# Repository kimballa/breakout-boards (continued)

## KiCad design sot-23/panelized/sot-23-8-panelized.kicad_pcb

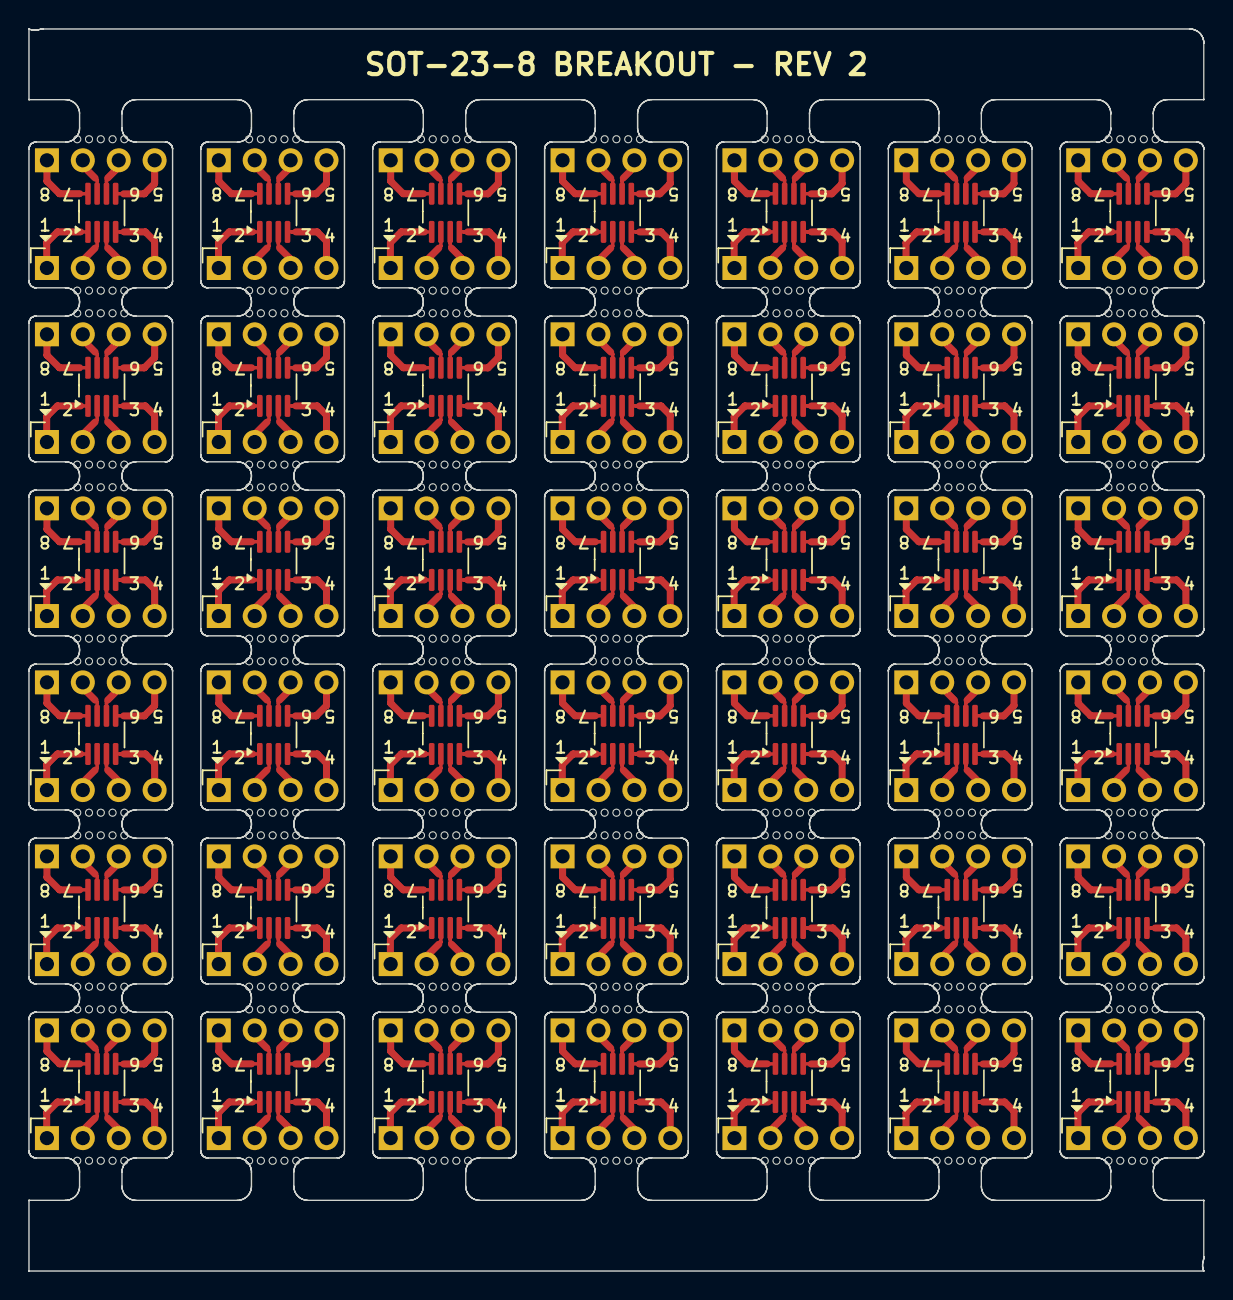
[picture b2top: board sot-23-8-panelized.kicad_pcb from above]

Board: 2 copper layers, 83.1 x 87.9 mm, 546 parts (0 on the bottom side), 336 nets.

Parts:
J3, J3#2, J3#3, J3#4, J3#5, J3#6, J3#7, J3#8, J3#9, J3#10, J3#11, J3#12, J3#13, J3#14, J3#15, J3#16, J3#17, J3#18, J3#19, J3#20, J3#21, J3#22, J3#23, J3#24, J3#25, J3#26, J3#27, J3#28, J3#29, J3#30, J3#31, J3#32, J3#33, J3#34, J3#35, J3#36, J3#37, J3#38, J3#39, J3#40, J3#41, J3#42, J4, J4#2, J4#3, J4#4, J4#5, J4#6, J4#7, J4#8, J4#9, J4#10, J4#11, J4#12, J4#13, J4#14, J4#15, J4#16, J4#17, J4#18, J4#19, J4#20, J4#21, J4#22, J4#23, J4#24, J4#25, J4#26, J4#27, J4#28, J4#29, J4#30, J4#31, J4#32, J4#33, J4#34, J4#35, J4#36, J4#37, J4#38, J4#39, J4#40, J4#41, J4#42: Conn_01x04; PinHeader_1x04_P2.54mm_Vertical
KiKit_MB_1_2, KiKit_MB_1_3, KiKit_MB_1_4, KiKit_MB_1_5, KiKit_MB_1_6, KiKit_MB_2_2, KiKit_MB_2_3, KiKit_MB_2_4, KiKit_MB_2_5, KiKit_MB_2_6, KiKit_MB_3_2, KiKit_MB_3_3, KiKit_MB_3_4, KiKit_MB_3_5, KiKit_MB_3_6, KiKit_MB_4_2, KiKit_MB_4_3, KiKit_MB_4_4, KiKit_MB_4_5, KiKit_MB_4_6, KiKit_MB_5_2, KiKit_MB_5_3, KiKit_MB_5_4, KiKit_MB_5_5, KiKit_MB_5_6, KiKit_MB_6_2, KiKit_MB_6_3, KiKit_MB_6_4, KiKit_MB_6_5, KiKit_MB_6_6, KiKit_MB_7_2, KiKit_MB_7_3, KiKit_MB_7_4, KiKit_MB_7_5, KiKit_MB_7_6, KiKit_MB_8_2, KiKit_MB_8_3, KiKit_MB_8_4, KiKit_MB_8_5, KiKit_MB_8_6, KiKit_MB_9_2, KiKit_MB_9_3, KiKit_MB_9_4, KiKit_MB_9_5, KiKit_MB_9_6, KiKit_MB_10_2, KiKit_MB_10_3, KiKit_MB_10_4, KiKit_MB_10_5, KiKit_MB_10_6, KiKit_MB_11_2, KiKit_MB_11_3, KiKit_MB_11_4, KiKit_MB_11_5, KiKit_MB_11_6, KiKit_MB_12_2, KiKit_MB_12_3, KiKit_MB_12_4, KiKit_MB_12_5, KiKit_MB_12_6, KiKit_MB_13_2, KiKit_MB_13_3, KiKit_MB_13_4, KiKit_MB_13_5, KiKit_MB_13_6, KiKit_MB_14_2, KiKit_MB_14_3, KiKit_MB_14_4, KiKit_MB_14_5, KiKit_MB_14_6, KiKit_MB_15_2, KiKit_MB_15_3, KiKit_MB_15_4, KiKit_MB_15_5, KiKit_MB_15_6, KiKit_MB_16_2, KiKit_MB_16_3, KiKit_MB_16_4, KiKit_MB_16_5, KiKit_MB_16_6, KiKit_MB_17_2, KiKit_MB_17_3, KiKit_MB_17_4, KiKit_MB_17_5, KiKit_MB_17_6, KiKit_MB_18_2, KiKit_MB_18_3, KiKit_MB_18_4, KiKit_MB_18_5, KiKit_MB_18_6, KiKit_MB_19_2, KiKit_MB_19_3, KiKit_MB_19_4, KiKit_MB_19_5, KiKit_MB_19_6, KiKit_MB_20_2, KiKit_MB_20_3, KiKit_MB_20_4, KiKit_MB_20_5, KiKit_MB_20_6, KiKit_MB_21_2, KiKit_MB_21_3, KiKit_MB_21_4, KiKit_MB_21_5, KiKit_MB_21_6, KiKit_MB_22_2, KiKit_MB_22_3, KiKit_MB_22_4, KiKit_MB_22_5, KiKit_MB_22_6, KiKit_MB_23_2, KiKit_MB_23_3, KiKit_MB_23_4, KiKit_MB_23_5, KiKit_MB_23_6, KiKit_MB_24_2, KiKit_MB_24_3, KiKit_MB_24_4, KiKit_MB_24_5, KiKit_MB_24_6, KiKit_MB_25_2, KiKit_MB_25_3, KiKit_MB_25_4, KiKit_MB_25_5, KiKit_MB_25_6, KiKit_MB_26_2, KiKit_MB_26_3, KiKit_MB_26_4, KiKit_MB_26_5, KiKit_MB_26_6, KiKit_MB_27_2, KiKit_MB_27_3, KiKit_MB_27_4, KiKit_MB_27_5, KiKit_MB_27_6, KiKit_MB_28_2, KiKit_MB_28_3, KiKit_MB_28_4, KiKit_MB_28_5, KiKit_MB_28_6, KiKit_MB_29_2, KiKit_MB_29_3, KiKit_MB_29_4, KiKit_MB_29_5, KiKit_MB_29_6, KiKit_MB_30_2, KiKit_MB_30_3, KiKit_MB_30_4, KiKit_MB_30_5, KiKit_MB_30_6, KiKit_MB_31_2, KiKit_MB_31_3, KiKit_MB_31_4, KiKit_MB_31_5, KiKit_MB_31_6, KiKit_MB_32_2, KiKit_MB_32_3, KiKit_MB_32_4, KiKit_MB_32_5, KiKit_MB_32_6, KiKit_MB_33_2, KiKit_MB_33_3, KiKit_MB_33_4, KiKit_MB_33_5, KiKit_MB_33_6, KiKit_MB_34_2, KiKit_MB_34_3, KiKit_MB_34_4, KiKit_MB_34_5, KiKit_MB_34_6, KiKit_MB_35_2, KiKit_MB_35_3, KiKit_MB_35_4, KiKit_MB_35_5, KiKit_MB_35_6, KiKit_MB_36_2, KiKit_MB_36_3, KiKit_MB_36_4, KiKit_MB_36_5, KiKit_MB_36_6, KiKit_MB_37_2, KiKit_MB_37_3, KiKit_MB_37_4, KiKit_MB_37_5, KiKit_MB_37_6, KiKit_MB_38_2, KiKit_MB_38_3, KiKit_MB_38_4, KiKit_MB_38_5, KiKit_MB_38_6, KiKit_MB_39_2, KiKit_MB_39_3, KiKit_MB_39_4, KiKit_MB_39_5, KiKit_MB_39_6, KiKit_MB_40_2, KiKit_MB_40_3, KiKit_MB_40_4, KiKit_MB_40_5, KiKit_MB_40_6, KiKit_MB_41_2, KiKit_MB_41_3, KiKit_MB_41_4, KiKit_MB_41_5, KiKit_MB_41_6, KiKit_MB_42_2, KiKit_MB_42_3, KiKit_MB_42_4, KiKit_MB_42_5, KiKit_MB_42_6, KiKit_MB_43_2, KiKit_MB_43_3, KiKit_MB_43_4, KiKit_MB_43_5, KiKit_MB_43_6, KiKit_MB_44_2, KiKit_MB_44_3, KiKit_MB_44_4, KiKit_MB_44_5, KiKit_MB_44_6, KiKit_MB_45_2, KiKit_MB_45_3, KiKit_MB_45_4, KiKit_MB_45_5, KiKit_MB_45_6, KiKit_MB_46_2, KiKit_MB_46_3, KiKit_MB_46_4, KiKit_MB_46_5, KiKit_MB_46_6, KiKit_MB_47_2, KiKit_MB_47_3, KiKit_MB_47_4, KiKit_MB_47_5, KiKit_MB_47_6, KiKit_MB_48_2, KiKit_MB_48_3, KiKit_MB_48_4, KiKit_MB_48_5, KiKit_MB_48_6, KiKit_MB_49_2, KiKit_MB_49_3, KiKit_MB_49_4, KiKit_MB_49_5, KiKit_MB_49_6, KiKit_MB_50_2, KiKit_MB_50_3, KiKit_MB_50_4, KiKit_MB_50_5, KiKit_MB_50_6, KiKit_MB_51_2, KiKit_MB_51_3, KiKit_MB_51_4, KiKit_MB_51_5, KiKit_MB_51_6, KiKit_MB_52_2, KiKit_MB_52_3, KiKit_MB_52_4, KiKit_MB_52_5, KiKit_MB_52_6, KiKit_MB_53_2, KiKit_MB_53_3, KiKit_MB_53_4, KiKit_MB_53_5, KiKit_MB_53_6, KiKit_MB_54_2, KiKit_MB_54_3, KiKit_MB_54_4, KiKit_MB_54_5, KiKit_MB_54_6, KiKit_MB_55_2, KiKit_MB_55_3, KiKit_MB_55_4, KiKit_MB_55_5, KiKit_MB_55_6, KiKit_MB_56_2, KiKit_MB_56_3, KiKit_MB_56_4, KiKit_MB_56_5, KiKit_MB_56_6, KiKit_MB_57_2, KiKit_MB_57_3, KiKit_MB_57_4, KiKit_MB_57_5, KiKit_MB_57_6, KiKit_MB_58_2, KiKit_MB_58_3, KiKit_MB_58_4, KiKit_MB_58_5, KiKit_MB_58_6, KiKit_MB_59_2, KiKit_MB_59_3, KiKit_MB_59_4, KiKit_MB_59_5, KiKit_MB_59_6, KiKit_MB_60_2, KiKit_MB_60_3, KiKit_MB_60_4, KiKit_MB_60_5, KiKit_MB_60_6, KiKit_MB_61_2, KiKit_MB_61_3, KiKit_MB_61_4, KiKit_MB_61_5, KiKit_MB_61_6, KiKit_MB_62_2, KiKit_MB_62_3, KiKit_MB_62_4, KiKit_MB_62_5, KiKit_MB_62_6, KiKit_MB_63_2, KiKit_MB_63_3, KiKit_MB_63_4, KiKit_MB_63_5, KiKit_MB_63_6, KiKit_MB_64_2, KiKit_MB_64_3, KiKit_MB_64_4, KiKit_MB_64_5, KiKit_MB_64_6, KiKit_MB_65_2, KiKit_MB_65_3, KiKit_MB_65_4, KiKit_MB_65_5, KiKit_MB_65_6, KiKit_MB_66_2, KiKit_MB_66_3, KiKit_MB_66_4, KiKit_MB_66_5, KiKit_MB_66_6, KiKit_MB_67_2, KiKit_MB_67_3, KiKit_MB_67_4, KiKit_MB_67_5, KiKit_MB_67_6, KiKit_MB_68_2, KiKit_MB_68_3, KiKit_MB_68_4, KiKit_MB_68_5, KiKit_MB_68_6, KiKit_MB_69_2, KiKit_MB_69_3, KiKit_MB_69_4, KiKit_MB_69_5, KiKit_MB_69_6, KiKit_MB_70_2, KiKit_MB_70_3, KiKit_MB_70_4, KiKit_MB_70_5, KiKit_MB_70_6, KiKit_MB_71_2, KiKit_MB_71_3, KiKit_MB_71_4, KiKit_MB_71_5, KiKit_MB_71_6, KiKit_MB_72_2, KiKit_MB_72_3, KiKit_MB_72_4, KiKit_MB_72_5, KiKit_MB_72_6, KiKit_MB_73_2, KiKit_MB_73_3, KiKit_MB_73_4, KiKit_MB_73_5, KiKit_MB_73_6, KiKit_MB_74_2, KiKit_MB_74_3, KiKit_MB_74_4, KiKit_MB_74_5, KiKit_MB_74_6, KiKit_MB_75_2, KiKit_MB_75_3, KiKit_MB_75_4, KiKit_MB_75_5, KiKit_MB_75_6, KiKit_MB_76_2, KiKit_MB_76_3, KiKit_MB_76_4, KiKit_MB_76_5, KiKit_MB_76_6, KiKit_MB_77_2, KiKit_MB_77_3, KiKit_MB_77_4, KiKit_MB_77_5, KiKit_MB_77_6, KiKit_MB_78_2, KiKit_MB_78_3, KiKit_MB_78_4, KiKit_MB_78_5, KiKit_MB_78_6, KiKit_MB_79_2, KiKit_MB_79_3, KiKit_MB_79_4, KiKit_MB_79_5, KiKit_MB_79_6, KiKit_MB_80_2, KiKit_MB_80_3, KiKit_MB_80_4, KiKit_MB_80_5, KiKit_MB_80_6, KiKit_MB_81_2, KiKit_MB_81_3, KiKit_MB_81_4, KiKit_MB_81_5, KiKit_MB_81_6, KiKit_MB_82_2, KiKit_MB_82_3, KiKit_MB_82_4, KiKit_MB_82_5, KiKit_MB_82_6, KiKit_MB_83_2, KiKit_MB_83_3, KiKit_MB_83_4, KiKit_MB_83_5, KiKit_MB_83_6, KiKit_MB_84_2, KiKit_MB_84_3, KiKit_MB_84_4, KiKit_MB_84_5, KiKit_MB_84_6: NPTH
U1, U1#2, U1#3, U1#4, U1#5, U1#6, U1#7, U1#8, U1#9, U1#10, U1#11, U1#12, U1#13, U1#14, U1#15, U1#16, U1#17, U1#18, U1#19, U1#20, U1#21, U1#22, U1#23, U1#24, U1#25, U1#26, U1#27, U1#28, U1#29, U1#30, U1#31, U1#32, U1#33, U1#34, U1#35, U1#36, U1#37, U1#38, U1#39, U1#40, U1#41, U1#42: THVD8000; SOT-23-8_Handsoldering

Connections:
Board_0-Net-(J3-Pin_1): J3#17.1, U1#13.1 (R)
Board_0-Net-(J3-Pin_2): J3#17.2, U1#13.2 (MODE)
Board_0-Net-(J3-Pin_3): J3#17.3, U1#13.3 (F_SET)
Board_0-Net-(J3-Pin_4): J3#17.4, U1#13.4 (D)
Board_0-Net-(J4-Pin_1): J4#26.1, U1#13.8 (VCC)
Board_0-Net-(J4-Pin_2): J4#26.2, U1#13.7 (B)
Board_0-Net-(J4-Pin_3): J4#26.3, U1#13.6 (A)
Board_0-Net-(J4-Pin_4): J4#26.4, U1#13.5 (GND)
Board_1-Net-(J3-Pin_1): J3#15.1, U1#28.1 (R)
Board_1-Net-(J3-Pin_2): J3#15.2, U1#28.2 (MODE)
Board_1-Net-(J3-Pin_3): J3#15.3, U1#28.3 (F_SET)
Board_1-Net-(J3-Pin_4): J3#15.4, U1#28.4 (D)
Board_1-Net-(J4-Pin_1): J4#5.1, U1#28.8 (VCC)
Board_1-Net-(J4-Pin_2): J4#5.2, U1#28.7 (B)
Board_1-Net-(J4-Pin_3): J4#5.3, U1#28.6 (A)
Board_1-Net-(J4-Pin_4): J4#5.4, U1#28.5 (GND)
Board_2-Net-(J3-Pin_1): J3#27.1, U1#10.1 (R)
Board_2-Net-(J3-Pin_2): J3#27.2, U1#10.2 (MODE)
Board_2-Net-(J3-Pin_3): J3#27.3, U1#10.3 (F_SET)
Board_2-Net-(J3-Pin_4): J3#27.4, U1#10.4 (D)
Board_2-Net-(J4-Pin_1): J4#31.1, U1#10.8 (VCC)
Board_2-Net-(J4-Pin_2): J4#31.2, U1#10.7 (B)
Board_2-Net-(J4-Pin_3): J4#31.3, U1#10.6 (A)
Board_2-Net-(J4-Pin_4): J4#31.4, U1#10.5 (GND)
Board_3-Net-(J3-Pin_1): J3#4.1, U1#11.1 (R)
Board_3-Net-(J3-Pin_2): J3#4.2, U1#11.2 (MODE)
Board_3-Net-(J3-Pin_3): J3#4.3, U1#11.3 (F_SET)
Board_3-Net-(J3-Pin_4): J3#4.4, U1#11.4 (D)
Board_3-Net-(J4-Pin_1): J4#29.1, U1#11.8 (VCC)
Board_3-Net-(J4-Pin_2): J4#29.2, U1#11.7 (B)
Board_3-Net-(J4-Pin_3): J4#29.3, U1#11.6 (A)
Board_3-Net-(J4-Pin_4): J4#29.4, U1#11.5 (GND)
Board_4-Net-(J3-Pin_1): J3#6.1, U1#34.1 (R)
Board_4-Net-(J3-Pin_2): J3#6.2, U1#34.2 (MODE)
Board_4-Net-(J3-Pin_3): J3#6.3, U1#34.3 (F_SET)
Board_4-Net-(J3-Pin_4): J3#6.4, U1#34.4 (D)
Board_4-Net-(J4-Pin_1): J4#24.1, U1#34.8 (VCC)
Board_4-Net-(J4-Pin_2): J4#24.2, U1#34.7 (B)
Board_4-Net-(J4-Pin_3): J4#24.3, U1#34.6 (A)
Board_4-Net-(J4-Pin_4): J4#24.4, U1#34.5 (GND)
Board_5-Net-(J3-Pin_1): J3#29.1, U1#35.1 (R)
Board_5-Net-(J3-Pin_2): J3#29.2, U1#35.2 (MODE)
Board_5-Net-(J3-Pin_3): J3#29.3, U1#35.3 (F_SET)
Board_5-Net-(J3-Pin_4): J3#29.4, U1#35.4 (D)
Board_5-Net-(J4-Pin_1): J4.1, U1#35.8 (VCC)
Board_5-Net-(J4-Pin_2): J4.2, U1#35.7 (B)
Board_5-Net-(J4-Pin_3): J4.3, U1#35.6 (A)
Board_5-Net-(J4-Pin_4): J4.4, U1#35.5 (GND)
Board_6-Net-(J3-Pin_1): J3#11.1, U1#2.1 (R)
Board_6-Net-(J3-Pin_2): J3#11.2, U1#2.2 (MODE)
Board_6-Net-(J3-Pin_3): J3#11.3, U1#2.3 (F_SET)
Board_6-Net-(J3-Pin_4): J3#11.4, U1#2.4 (D)
Board_6-Net-(J4-Pin_1): J4#3.1, U1#2.8 (VCC)
Board_6-Net-(J4-Pin_2): J4#3.2, U1#2.7 (B)
Board_6-Net-(J4-Pin_3): J4#3.3, U1#2.6 (A)
Board_6-Net-(J4-Pin_4): J4#3.4, U1#2.5 (GND)
Board_7-Net-(J3-Pin_1): J3#28.1, U1#9.1 (R)
Board_7-Net-(J3-Pin_2): J3#28.2, U1#9.2 (MODE)
Board_7-Net-(J3-Pin_3): J3#28.3, U1#9.3 (F_SET)
Board_7-Net-(J3-Pin_4): J3#28.4, U1#9.4 (D)
Board_7-Net-(J4-Pin_1): J4#37.1, U1#9.8 (VCC)
Board_7-Net-(J4-Pin_2): J4#37.2, U1#9.7 (B)
Board_7-Net-(J4-Pin_3): J4#37.3, U1#9.6 (A)
Board_7-Net-(J4-Pin_4): J4#37.4, U1#9.5 (GND)
Board_8-Net-(J3-Pin_1): J3#26.1, U1#6.1 (R)
Board_8-Net-(J3-Pin_2): J3#26.2, U1#6.2 (MODE)
Board_8-Net-(J3-Pin_3): J3#26.3, U1#6.3 (F_SET)
Board_8-Net-(J3-Pin_4): J3#26.4, U1#6.4 (D)
Board_8-Net-(J4-Pin_1): J4#12.1, U1#6.8 (VCC)
Board_8-Net-(J4-Pin_2): J4#12.2, U1#6.7 (B)
Board_8-Net-(J4-Pin_3): J4#12.3, U1#6.6 (A)
Board_8-Net-(J4-Pin_4): J4#12.4, U1#6.5 (GND)
Board_9-Net-(J3-Pin_1): J3#8.1, U1#15.1 (R)
Board_9-Net-(J3-Pin_2): J3#8.2, U1#15.2 (MODE)
Board_9-Net-(J3-Pin_3): J3#8.3, U1#15.3 (F_SET)
Board_9-Net-(J3-Pin_4): J3#8.4, U1#15.4 (D)
Board_9-Net-(J4-Pin_1): J4#33.1, U1#15.8 (VCC)
Board_9-Net-(J4-Pin_2): J4#33.2, U1#15.7 (B)
Board_9-Net-(J4-Pin_3): J4#33.3, U1#15.6 (A)
Board_9-Net-(J4-Pin_4): J4#33.4, U1#15.5 (GND)
Board_10-Net-(J3-Pin_1): J3#19.1, U1#18.1 (R)
Board_10-Net-(J3-Pin_2): J3#19.2, U1#18.2 (MODE)
Board_10-Net-(J3-Pin_3): J3#19.3, U1#18.3 (F_SET)
Board_10-Net-(J3-Pin_4): J3#19.4, U1#18.4 (D)
Board_10-Net-(J4-Pin_1): J4#9.1, U1#18.8 (VCC)
Board_10-Net-(J4-Pin_2): J4#9.2, U1#18.7 (B)
Board_10-Net-(J4-Pin_3): J4#9.3, U1#18.6 (A)
Board_10-Net-(J4-Pin_4): J4#9.4, U1#18.5 (GND)
Board_11-Net-(J3-Pin_1): J3#22.1, U1#22.1 (R)
Board_11-Net-(J3-Pin_2): J3#22.2, U1#22.2 (MODE)
Board_11-Net-(J3-Pin_3): J3#22.3, U1#22.3 (F_SET)
Board_11-Net-(J3-Pin_4): J3#22.4, U1#22.4 (D)
Board_11-Net-(J4-Pin_1): J4#25.1, U1#22.8 (VCC)
Board_11-Net-(J4-Pin_2): J4#25.2, U1#22.7 (B)
Board_11-Net-(J4-Pin_3): J4#25.3, U1#22.6 (A)
Board_11-Net-(J4-Pin_4): J4#25.4, U1#22.5 (GND)
Board_12-Net-(J3-Pin_1): J3.1, U1#30.1 (R)
Board_12-Net-(J3-Pin_2): J3.2, U1#30.2 (MODE)
Board_12-Net-(J3-Pin_3): J3.3, U1#30.3 (F_SET)
Board_12-Net-(J3-Pin_4): J3.4, U1#30.4 (D)
Board_12-Net-(J4-Pin_1): J4#7.1, U1#30.8 (VCC)
Board_12-Net-(J4-Pin_2): J4#7.2, U1#30.7 (B)
Board_12-Net-(J4-Pin_3): J4#7.3, U1#30.6 (A)
Board_12-Net-(J4-Pin_4): J4#7.4, U1#30.5 (GND)
Board_13-Net-(J3-Pin_1): J3#3.1, U1#41.1 (R)
Board_13-Net-(J3-Pin_2): J3#3.2, U1#41.2 (MODE)
Board_13-Net-(J3-Pin_3): J3#3.3, U1#41.3 (F_SET)
Board_13-Net-(J3-Pin_4): J3#3.4, U1#41.4 (D)
Board_13-Net-(J4-Pin_1): J4#32.1, U1#41.8 (VCC)
Board_13-Net-(J4-Pin_2): J4#32.2, U1#41.7 (B)
Board_13-Net-(J4-Pin_3): J4#32.3, U1#41.6 (A)
Board_13-Net-(J4-Pin_4): J4#32.4, U1#41.5 (GND)
Board_14-Net-(J3-Pin_1): J3#31.1, U1#26.1 (R)
Board_14-Net-(J3-Pin_2): J3#31.2, U1#26.2 (MODE)
Board_14-Net-(J3-Pin_3): J3#31.3, U1#26.3 (F_SET)
Board_14-Net-(J3-Pin_4): J3#31.4, U1#26.4 (D)
Board_14-Net-(J4-Pin_1): J4#34.1, U1#26.8 (VCC)
Board_14-Net-(J4-Pin_2): J4#34.2, U1#26.7 (B)
Board_14-Net-(J4-Pin_3): J4#34.3, U1#26.6 (A)
Board_14-Net-(J4-Pin_4): J4#34.4, U1#26.5 (GND)
Board_15-Net-(J3-Pin_1): J3#36.1, U1#29.1 (R)
Board_15-Net-(J3-Pin_2): J3#36.2, U1#29.2 (MODE)
Board_15-Net-(J3-Pin_3): J3#36.3, U1#29.3 (F_SET)
Board_15-Net-(J3-Pin_4): J3#36.4, U1#29.4 (D)
Board_15-Net-(J4-Pin_1): J4#13.1, U1#29.8 (VCC)
Board_15-Net-(J4-Pin_2): J4#13.2, U1#29.7 (B)
Board_15-Net-(J4-Pin_3): J4#13.3, U1#29.6 (A)
Board_15-Net-(J4-Pin_4): J4#13.4, U1#29.5 (GND)
Board_16-Net-(J3-Pin_1): J3#9.1, U1#31.1 (R)
Board_16-Net-(J3-Pin_2): J3#9.2, U1#31.2 (MODE)
Board_16-Net-(J3-Pin_3): J3#9.3, U1#31.3 (F_SET)
Board_16-Net-(J3-Pin_4): J3#9.4, U1#31.4 (D)
Board_16-Net-(J4-Pin_1): J4#39.1, U1#31.8 (VCC)
Board_16-Net-(J4-Pin_2): J4#39.2, U1#31.7 (B)
Board_16-Net-(J4-Pin_3): J4#39.3, U1#31.6 (A)
Board_16-Net-(J4-Pin_4): J4#39.4, U1#31.5 (GND)
Board_17-Net-(J3-Pin_1): J3#16.1, U1#12.1 (R)
Board_17-Net-(J3-Pin_2): J3#16.2, U1#12.2 (MODE)
Board_17-Net-(J3-Pin_3): J3#16.3, U1#12.3 (F_SET)
Board_17-Net-(J3-Pin_4): J3#16.4, U1#12.4 (D)
Board_17-Net-(J4-Pin_1): J4#23.1, U1#12.8 (VCC)
Board_17-Net-(J4-Pin_2): J4#23.2, U1#12.7 (B)
Board_17-Net-(J4-Pin_3): J4#23.3, U1#12.6 (A)
Board_17-Net-(J4-Pin_4): J4#23.4, U1#12.5 (GND)
Board_18-Net-(J3-Pin_1): J3#40.1, U1#27.1 (R)
Board_18-Net-(J3-Pin_2): J3#40.2, U1#27.2 (MODE)
Board_18-Net-(J3-Pin_3): J3#40.3, U1#27.3 (F_SET)
Board_18-Net-(J3-Pin_4): J3#40.4, U1#27.4 (D)
Board_18-Net-(J4-Pin_1): J4#16.1, U1#27.8 (VCC)
Board_18-Net-(J4-Pin_2): J4#16.2, U1#27.7 (B)
Board_18-Net-(J4-Pin_3): J4#16.3, U1#27.6 (A)
Board_18-Net-(J4-Pin_4): J4#16.4, U1#27.5 (GND)
Board_19-Net-(J3-Pin_1): J3#5.1, U1#8.1 (R)
Board_19-Net-(J3-Pin_2): J3#5.2, U1#8.2 (MODE)
Board_19-Net-(J3-Pin_3): J3#5.3, U1#8.3 (F_SET)
Board_19-Net-(J3-Pin_4): J3#5.4, U1#8.4 (D)
Board_19-Net-(J4-Pin_1): J4#8.1, U1#8.8 (VCC)
Board_19-Net-(J4-Pin_2): J4#8.2, U1#8.7 (B)
Board_19-Net-(J4-Pin_3): J4#8.3, U1#8.6 (A)
Board_19-Net-(J4-Pin_4): J4#8.4, U1#8.5 (GND)
Board_20-Net-(J3-Pin_1): J3#24.1, U1#37.1 (R)
Board_20-Net-(J3-Pin_2): J3#24.2, U1#37.2 (MODE)
Board_20-Net-(J3-Pin_3): J3#24.3, U1#37.3 (F_SET)
Board_20-Net-(J3-Pin_4): J3#24.4, U1#37.4 (D)
Board_20-Net-(J4-Pin_1): J4#20.1, U1#37.8 (VCC)
Board_20-Net-(J4-Pin_2): J4#20.2, U1#37.7 (B)
Board_20-Net-(J4-Pin_3): J4#20.3, U1#37.6 (A)
Board_20-Net-(J4-Pin_4): J4#20.4, U1#37.5 (GND)
Board_21-Net-(J3-Pin_1): J3#38.1, U1#14.1 (R)
Board_21-Net-(J3-Pin_2): J3#38.2, U1#14.2 (MODE)
Board_21-Net-(J3-Pin_3): J3#38.3, U1#14.3 (F_SET)
Board_21-Net-(J3-Pin_4): J3#38.4, U1#14.4 (D)
Board_21-Net-(J4-Pin_1): J4#30.1, U1#14.8 (VCC)
Board_21-Net-(J4-Pin_2): J4#30.2, U1#14.7 (B)
Board_21-Net-(J4-Pin_3): J4#30.3, U1#14.6 (A)
Board_21-Net-(J4-Pin_4): J4#30.4, U1#14.5 (GND)
Board_22-Net-(J3-Pin_1): J3#30.1, U1#40.1 (R)
Board_22-Net-(J3-Pin_2): J3#30.2, U1#40.2 (MODE)
Board_22-Net-(J3-Pin_3): J3#30.3, U1#40.3 (F_SET)
Board_22-Net-(J3-Pin_4): J3#30.4, U1#40.4 (D)
Board_22-Net-(J4-Pin_1): J4#14.1, U1#40.8 (VCC)
Board_22-Net-(J4-Pin_2): J4#14.2, U1#40.7 (B)
Board_22-Net-(J4-Pin_3): J4#14.3, U1#40.6 (A)
Board_22-Net-(J4-Pin_4): J4#14.4, U1#40.5 (GND)
Board_23-Net-(J3-Pin_1): J3#7.1, U1#5.1 (R)
Board_23-Net-(J3-Pin_2): J3#7.2, U1#5.2 (MODE)
Board_23-Net-(J3-Pin_3): J3#7.3, U1#5.3 (F_SET)
Board_23-Net-(J3-Pin_4): J3#7.4, U1#5.4 (D)
Board_23-Net-(J4-Pin_1): J4#35.1, U1#5.8 (VCC)
Board_23-Net-(J4-Pin_2): J4#35.2, U1#5.7 (B)
Board_23-Net-(J4-Pin_3): J4#35.3, U1#5.6 (A)
Board_23-Net-(J4-Pin_4): J4#35.4, U1#5.5 (GND)
Board_24-Net-(J3-Pin_1): J3#20.1, U1#39.1 (R)
Board_24-Net-(J3-Pin_2): J3#20.2, U1#39.2 (MODE)
Board_24-Net-(J3-Pin_3): J3#20.3, U1#39.3 (F_SET)
Board_24-Net-(J3-Pin_4): J3#20.4, U1#39.4 (D)
Board_24-Net-(J4-Pin_1): J4#22.1, U1#39.8 (VCC)
Board_24-Net-(J4-Pin_2): J4#22.2, U1#39.7 (B)
Board_24-Net-(J4-Pin_3): J4#22.3, U1#39.6 (A)
Board_24-Net-(J4-Pin_4): J4#22.4, U1#39.5 (GND)
Board_25-Net-(J3-Pin_1): J3#42.1, U1.1 (R)
Board_25-Net-(J3-Pin_2): J3#42.2, U1.2 (MODE)
Board_25-Net-(J3-Pin_3): J3#42.3, U1.3 (F_SET)
Board_25-Net-(J3-Pin_4): J3#42.4, U1.4 (D)
Board_25-Net-(J4-Pin_1): J4#15.1, U1.8 (VCC)
Board_25-Net-(J4-Pin_2): J4#15.2, U1.7 (B)
Board_25-Net-(J4-Pin_3): J4#15.3, U1.6 (A)
Board_25-Net-(J4-Pin_4): J4#15.4, U1.5 (GND)
Board_26-Net-(J3-Pin_1): J3#21.1, U1#17.1 (R)
Board_26-Net-(J3-Pin_2): J3#21.2, U1#17.2 (MODE)
Board_26-Net-(J3-Pin_3): J3#21.3, U1#17.3 (F_SET)
Board_26-Net-(J3-Pin_4): J3#21.4, U1#17.4 (D)
Board_26-Net-(J4-Pin_1): J4#17.1, U1#17.8 (VCC)
Board_26-Net-(J4-Pin_2): J4#17.2, U1#17.7 (B)
Board_26-Net-(J4-Pin_3): J4#17.3, U1#17.6 (A)
Board_26-Net-(J4-Pin_4): J4#17.4, U1#17.5 (GND)
Board_27-Net-(J3-Pin_1): J3#35.1, U1#36.1 (R)
Board_27-Net-(J3-Pin_2): J3#35.2, U1#36.2 (MODE)
Board_27-Net-(J3-Pin_3): J3#35.3, U1#36.3 (F_SET)
Board_27-Net-(J3-Pin_4): J3#35.4, U1#36.4 (D)
Board_27-Net-(J4-Pin_1): J4#21.1, U1#36.8 (VCC)
Board_27-Net-(J4-Pin_2): J4#21.2, U1#36.7 (B)
Board_27-Net-(J4-Pin_3): J4#21.3, U1#36.6 (A)
Board_27-Net-(J4-Pin_4): J4#21.4, U1#36.5 (GND)
Board_28-Net-(J3-Pin_1): J3#14.1, U1#7.1 (R)
Board_28-Net-(J3-Pin_2): J3#14.2, U1#7.2 (MODE)
Board_28-Net-(J3-Pin_3): J3#14.3, U1#7.3 (F_SET)
Board_28-Net-(J3-Pin_4): J3#14.4, U1#7.4 (D)
Board_28-Net-(J4-Pin_1): J4#41.1, U1#7.8 (VCC)
Board_28-Net-(J4-Pin_2): J4#41.2, U1#7.7 (B)
Board_28-Net-(J4-Pin_3): J4#41.3, U1#7.6 (A)
Board_28-Net-(J4-Pin_4): J4#41.4, U1#7.5 (GND)
Board_29-Net-(J3-Pin_1): J3#12.1, U1#25.1 (R)
Board_29-Net-(J3-Pin_2): J3#12.2, U1#25.2 (MODE)
Board_29-Net-(J3-Pin_3): J3#12.3, U1#25.3 (F_SET)
Board_29-Net-(J3-Pin_4): J3#12.4, U1#25.4 (D)
Board_29-Net-(J4-Pin_1): J4#6.1, U1#25.8 (VCC)
Board_29-Net-(J4-Pin_2): J4#6.2, U1#25.7 (B)
Board_29-Net-(J4-Pin_3): J4#6.3, U1#25.6 (A)
Board_29-Net-(J4-Pin_4): J4#6.4, U1#25.5 (GND)
Board_30-Net-(J3-Pin_1): J3#34.1, U1#32.1 (R)
Board_30-Net-(J3-Pin_2): J3#34.2, U1#32.2 (MODE)
Board_30-Net-(J3-Pin_3): J3#34.3, U1#32.3 (F_SET)
Board_30-Net-(J3-Pin_4): J3#34.4, U1#32.4 (D)
Board_30-Net-(J4-Pin_1): J4#11.1, U1#32.8 (VCC)
Board_30-Net-(J4-Pin_2): J4#11.2, U1#32.7 (B)
Board_30-Net-(J4-Pin_3): J4#11.3, U1#32.6 (A)
Board_30-Net-(J4-Pin_4): J4#11.4, U1#32.5 (GND)
Board_31-Net-(J3-Pin_1): J3#25.1, U1#19.1 (R)
Board_31-Net-(J3-Pin_2): J3#25.2, U1#19.2 (MODE)
Board_31-Net-(J3-Pin_3): J3#25.3, U1#19.3 (F_SET)
Board_31-Net-(J3-Pin_4): J3#25.4, U1#19.4 (D)
Board_31-Net-(J4-Pin_1): J4#4.1, U1#19.8 (VCC)
Board_31-Net-(J4-Pin_2): J4#4.2, U1#19.7 (B)
Board_31-Net-(J4-Pin_3): J4#4.3, U1#19.6 (A)
Board_31-Net-(J4-Pin_4): J4#4.4, U1#19.5 (GND)
Board_32-Net-(J3-Pin_1): J3#32.1, U1#21.1 (R)
Board_32-Net-(J3-Pin_2): J3#32.2, U1#21.2 (MODE)
Board_32-Net-(J3-Pin_3): J3#32.3, U1#21.3 (F_SET)
Board_32-Net-(J3-Pin_4): J3#32.4, U1#21.4 (D)
Board_32-Net-(J4-Pin_1): J4#18.1, U1#21.8 (VCC)
Board_32-Net-(J4-Pin_2): J4#18.2, U1#21.7 (B)
Board_32-Net-(J4-Pin_3): J4#18.3, U1#21.6 (A)
Board_32-Net-(J4-Pin_4): J4#18.4, U1#21.5 (GND)
Board_33-Net-(J3-Pin_1): J3#39.1, U1#24.1 (R)
Board_33-Net-(J3-Pin_2): J3#39.2, U1#24.2 (MODE)
Board_33-Net-(J3-Pin_3): J3#39.3, U1#24.3 (F_SET)
Board_33-Net-(J3-Pin_4): J3#39.4, U1#24.4 (D)
Board_33-Net-(J4-Pin_1): J4#2.1, U1#24.8 (VCC)
Board_33-Net-(J4-Pin_2): J4#2.2, U1#24.7 (B)
Board_33-Net-(J4-Pin_3): J4#2.3, U1#24.6 (A)
Board_33-Net-(J4-Pin_4): J4#2.4, U1#24.5 (GND)
Board_34-Net-(J3-Pin_1): J3#37.1, U1#42.1 (R)
Board_34-Net-(J3-Pin_2): J3#37.2, U1#42.2 (MODE)
Board_34-Net-(J3-Pin_3): J3#37.3, U1#42.3 (F_SET)
Board_34-Net-(J3-Pin_4): J3#37.4, U1#42.4 (D)
Board_34-Net-(J4-Pin_1): J4#42.1, U1#42.8 (VCC)
Board_34-Net-(J4-Pin_2): J4#42.2, U1#42.7 (B)
Board_34-Net-(J4-Pin_3): J4#42.3, U1#42.6 (A)
Board_34-Net-(J4-Pin_4): J4#42.4, U1#42.5 (GND)
Board_35-Net-(J3-Pin_1): J3#41.1, U1#33.1 (R)
Board_35-Net-(J3-Pin_2): J3#41.2, U1#33.2 (MODE)
Board_35-Net-(J3-Pin_3): J3#41.3, U1#33.3 (F_SET)
Board_35-Net-(J3-Pin_4): J3#41.4, U1#33.4 (D)
Board_35-Net-(J4-Pin_1): J4#27.1, U1#33.8 (VCC)
Board_35-Net-(J4-Pin_2): J4#27.2, U1#33.7 (B)
Board_35-Net-(J4-Pin_3): J4#27.3, U1#33.6 (A)
Board_35-Net-(J4-Pin_4): J4#27.4, U1#33.5 (GND)
Board_36-Net-(J3-Pin_1): J3#18.1, U1#38.1 (R)
Board_36-Net-(J3-Pin_2): J3#18.2, U1#38.2 (MODE)
Board_36-Net-(J3-Pin_3): J3#18.3, U1#38.3 (F_SET)
Board_36-Net-(J3-Pin_4): J3#18.4, U1#38.4 (D)
Board_36-Net-(J4-Pin_1): J4#36.1, U1#38.8 (VCC)
Board_36-Net-(J4-Pin_2): J4#36.2, U1#38.7 (B)
Board_36-Net-(J4-Pin_3): J4#36.3, U1#38.6 (A)
Board_36-Net-(J4-Pin_4): J4#36.4, U1#38.5 (GND)
Board_37-Net-(J3-Pin_1): J3#2.1, U1#20.1 (R)
Board_37-Net-(J3-Pin_2): J3#2.2, U1#20.2 (MODE)
Board_37-Net-(J3-Pin_3): J3#2.3, U1#20.3 (F_SET)
Board_37-Net-(J3-Pin_4): J3#2.4, U1#20.4 (D)
Board_37-Net-(J4-Pin_1): J4#40.1, U1#20.8 (VCC)
Board_37-Net-(J4-Pin_2): J4#40.2, U1#20.7 (B)
Board_37-Net-(J4-Pin_3): J4#40.3, U1#20.6 (A)
Board_37-Net-(J4-Pin_4): J4#40.4, U1#20.5 (GND)
Board_38-Net-(J3-Pin_1): J3#10.1, U1#3.1 (R)
Board_38-Net-(J3-Pin_2): J3#10.2, U1#3.2 (MODE)
Board_38-Net-(J3-Pin_3): J3#10.3, U1#3.3 (F_SET)
Board_38-Net-(J3-Pin_4): J3#10.4, U1#3.4 (D)
Board_38-Net-(J4-Pin_1): J4#19.1, U1#3.8 (VCC)
Board_38-Net-(J4-Pin_2): J4#19.2, U1#3.7 (B)
Board_38-Net-(J4-Pin_3): J4#19.3, U1#3.6 (A)
Board_38-Net-(J4-Pin_4): J4#19.4, U1#3.5 (GND)
Board_39-Net-(J3-Pin_1): J3#23.1, U1#23.1 (R)
Board_39-Net-(J3-Pin_2): J3#23.2, U1#23.2 (MODE)
Board_39-Net-(J3-Pin_3): J3#23.3, U1#23.3 (F_SET)
Board_39-Net-(J3-Pin_4): J3#23.4, U1#23.4 (D)
Board_39-Net-(J4-Pin_1): J4#38.1, U1#23.8 (VCC)
Board_39-Net-(J4-Pin_2): J4#38.2, U1#23.7 (B)
Board_39-Net-(J4-Pin_3): J4#38.3, U1#23.6 (A)
Board_39-Net-(J4-Pin_4): J4#38.4, U1#23.5 (GND)
Board_40-Net-(J3-Pin_1): J3#33.1, U1#4.1 (R)
Board_40-Net-(J3-Pin_2): J3#33.2, U1#4.2 (MODE)
Board_40-Net-(J3-Pin_3): J3#33.3, U1#4.3 (F_SET)
Board_40-Net-(J3-Pin_4): J3#33.4, U1#4.4 (D)
Board_40-Net-(J4-Pin_1): J4#28.1, U1#4.8 (VCC)
Board_40-Net-(J4-Pin_2): J4#28.2, U1#4.7 (B)
Board_40-Net-(J4-Pin_3): J4#28.3, U1#4.6 (A)
Board_40-Net-(J4-Pin_4): J4#28.4, U1#4.5 (GND)
Board_41-Net-(J3-Pin_1): J3#13.1, U1#16.1 (R)
Board_41-Net-(J3-Pin_2): J3#13.2, U1#16.2 (MODE)
Board_41-Net-(J3-Pin_3): J3#13.3, U1#16.3 (F_SET)
Board_41-Net-(J3-Pin_4): J3#13.4, U1#16.4 (D)
Board_41-Net-(J4-Pin_1): J4#10.1, U1#16.8 (VCC)
Board_41-Net-(J4-Pin_2): J4#10.2, U1#16.7 (B)
Board_41-Net-(J4-Pin_3): J4#10.3, U1#16.6 (A)
Board_41-Net-(J4-Pin_4): J4#10.4, U1#16.5 (GND)
